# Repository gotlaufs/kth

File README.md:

# kth
Stuff for various KTH courses

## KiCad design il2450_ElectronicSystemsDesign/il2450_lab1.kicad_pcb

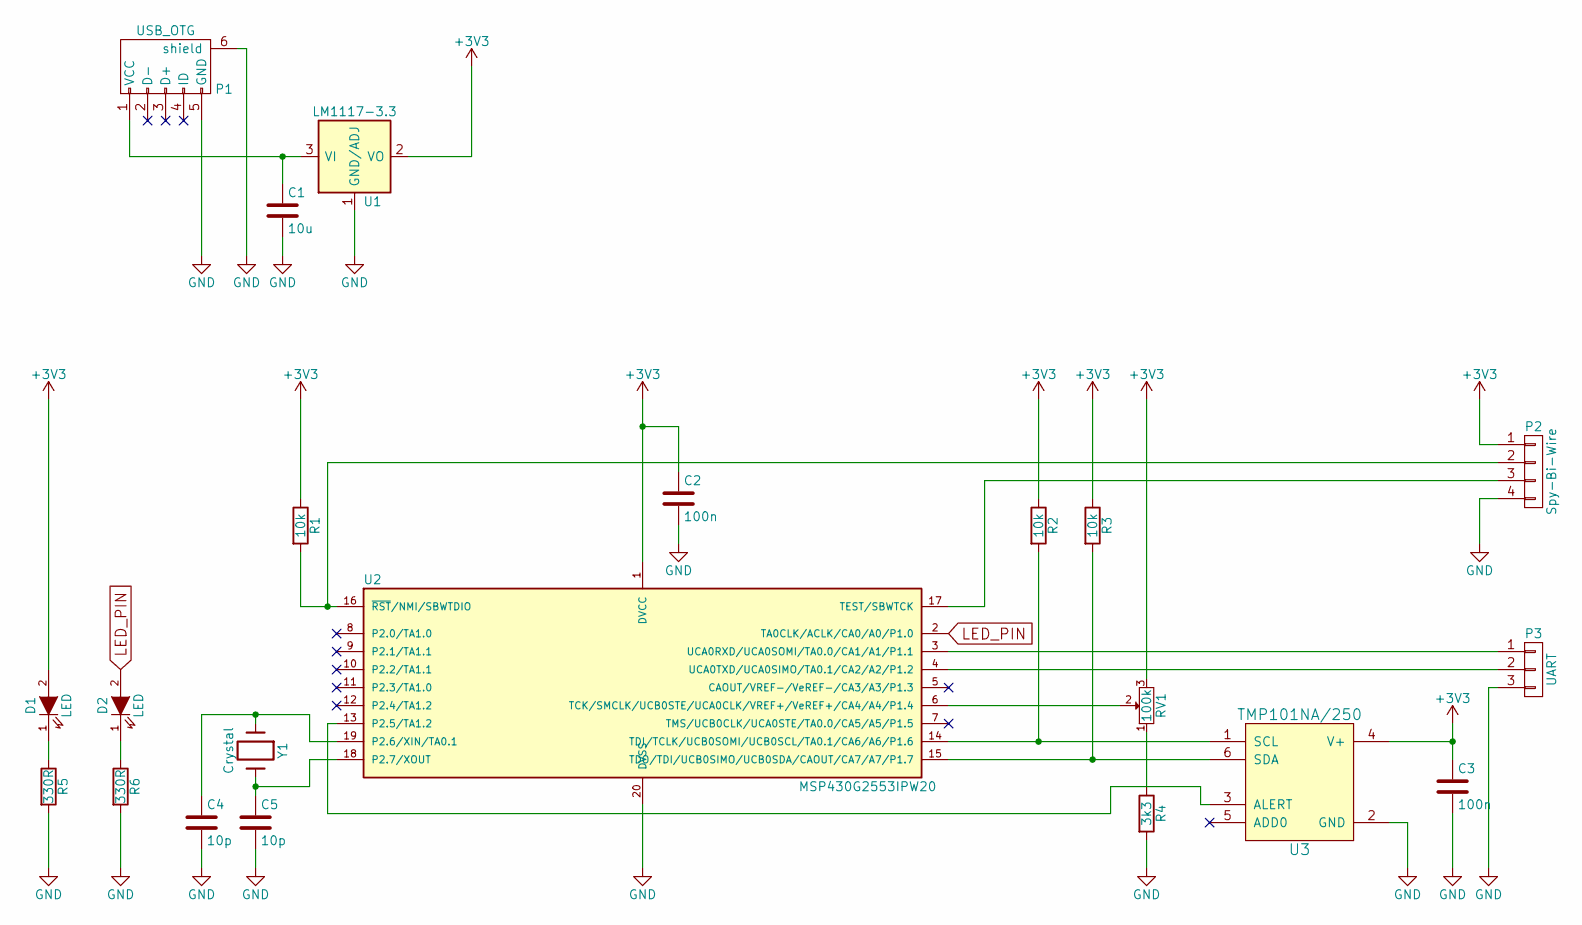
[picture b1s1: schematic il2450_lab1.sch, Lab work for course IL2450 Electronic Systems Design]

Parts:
C1: 10u; CP_Elec_6.3x5.3
C2, C3: 100n; C_0805_HandSoldering
C4, C5: 10p; C_0805_HandSoldering
D1, D2: LED; LED_0805
P1: USB_OTG; USB_Micro-B
P2: Spy-Bi-Wire; Pin_Header_Straight_1x04_Pitch2.54mm_SMD_Pin1Left
P3: UART; Pin_Header_Straight_1x03_Pitch2.54mm_SMD_Pin1Left
R1, R2, R3: 10k; R_0805_HandSoldering
R4: 3k3; R_0805_HandSoldering
R5, R6: 330R; R_0805_HandSoldering
RV1: 100k; Potentiometer_Trimmer-EVM3E
U1: LM1117-3.3; SOT-223
U2: MSP430G2553IPW20; TSSOP-20_4.4x6.5mm_Pitch0.65mm
U3: TMP101NA/250; SOT-23-6_Handsoldering
Y1: Crystal; Crystal_SMD_HC49-SD

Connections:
+3V3: C2.1, C3.1, D1.2 (A), P2.1, R1.1, R2.1, R3.1, RV1.3, U1.2 (VO), U1.4 (VO), U2.1 (DVCC), U3.4 (V+)
GND: C1.2, C2.2, C3.2, C4.2, C5.2, P1.5 (GND), P1.6 (shield), P2.4, P3.3, R4.2, R5.2, R6.2, U1.1 (GND/ADJ), U2.20 (DVSS), U3.2 (GND)
LED_PIN: D2.2 (A), U2.2 (TA0CLK/ACLK/CA0/A0/P1.0)
unnamed: C1.1, P1.1 (VCC), U1.3 (VI)
unnamed: C4.1, U2.19 (P2.6/XIN/TA0.1), Y1.1
unnamed: C5.1, U2.18 (P2.7/XOUT), Y1.2
unnamed: D1.1 (K), R5.1
unnamed: D2.1 (K), R6.1
unnamed: P2.2, R1.2, U2.16 (~RST~/NMI/SBWTDIO)
unnamed: P2.3, U2.17 (TEST/SBWTCK)
unnamed: P3.1, U2.3 (UCA0RXD/UCA0SOMI/TA0.0/CA1/A1/P1.1)
unnamed: P3.2, U2.4 (UCA0TXD/UCA0SIMO/TA0.1/CA2/A2/P1.2)
unnamed: R2.2, U2.14 (TDI/TCLK/UCB0SOMI/UCB0SCL/TA0.1/CA6/A6/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), U3.1 (SCL)
unnamed: R3.2, U2.15 (TDO/TDI/UCB0SIMO/UCB0SDA/CAOUT/CA7/A7/P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), U3.6 (SDA)
unnamed: R4.1, RV1.1
unnamed: RV1.2, U2.6 (TCK/SMCLK/UCB0STE/UCA0CLK/VREF+/VeREF+/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)
unnamed: U2.13 (P2.5/TA1.2), U3.3 (ALERT)

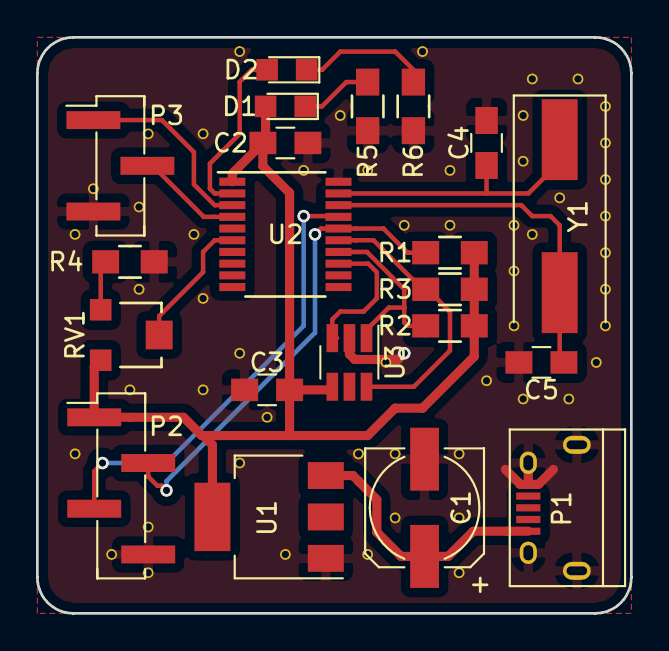
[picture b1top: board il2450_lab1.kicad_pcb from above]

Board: 2 copper layers, 33.0 x 32.0 mm, 21 parts (0 on the bottom side), 17 nets.

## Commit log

2017-03-30 PCB files for il2450 Electronic Systems Design
2017-03-30 Added board dimensions
2017-03-30 PCB exports and lab manual files for il2540
2017-03-30 Some more exports
